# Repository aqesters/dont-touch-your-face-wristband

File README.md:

# dont-touch-your-face-wristband
A wristband that vibrates when the wearer tries to touch their face

## System overview
First of all, the device must be worn on the inside of the wrist, facing towards the body when one's arm is by their side. 

The wristband functions by using two sensors: an accelerometer to measure arm position, and an IR optical sensor to measure proximity. The workflow is described below.
- The microcontroller remains in Sleep mode to conserve power until the arm is raised.
- Once the arm is raised - which is determined by an accelerometer threshold - the accelerometer wakes the microcontroller (MCU) via pin interrupt.
- The MCU remains in Active mode while the arm is raised. In Active mode, the MCU continuously polls the proximity sensor.
- If the proximity reading surpasses a certain threshold, the MCU triggers the vibration motor to alert the wearer.

Note that an alert will not be sent to the wearer unless both the arm is raised (accelerometer threshold) and the hand is close to the face (proximity threshold). This increases the likelihood that the wearer receives a vibration alert only if their hand is near their neck face.

## Cover glass for proximity sensor
In the assembly, the proximity sensor is purposely placed near the edge of the board. At this position, the sensor can detect proximity both above and beside the PCB. If using a cover glass, the following conditions must be met for best performance:
1. The cover glass must be made of IR-transparent material
2. The proximity sensor threshold may need to be increased, as cover glass will reflect some IR back to the sensor 
3. The cover glass should be curved such that the proximity sensor is sensitive to detection both above and near the edge of the PCB (see example)

Note that this implementation for proximity sensing is **PATENT PENDING**.

## Enclosure
The enclosure has been designed to be 3D-printable using PLA and a 0.2 mm nozzle. The design is compatible with off-the-shelf 18 mm wrist straps (see link).

[Amazon link to wrist straps](https://www.amazon.com/dp/B0C1RQ1HML)

The enclosure consists of a "bottom" (which the PCB sits in) and a "lid" (which is glued to the "bottom" to cover the PCB). The enclosure was designed using Onshape. The STEP files are included in `enclosure/`, and the Onshape design file can be accessed at the link below.

[Link to Onshape CAD file](https://cad.onshape.com/documents/f453aeea43687b5a9c082ca3/w/8d4d5c0042ac79ddd7b31543/e/8a52f216663301647b5c429d?renderMode=0&uiState=697bc61246433338537cc1be)

## Electronics
The Kicad design files, Gerber files, component datasheets, and bill of materials (BOM) are included in `electronics/`. The BOM includes components that can be assembled onto the board by PCB manufacturers. Not included in the BOM are the lithium polymer battery and the vibration motor. Links for those are provided below.

### Battery
The battery used in the initial version is a lithium polymer battery with a capacity of 110 mAh and dimensions of 28mm x 12mm x 4mm. The battery leads must be soldered to pads on the PCB.

The link points to a battery from LiPol battery, product number LP401228. Note that this is a foreign provider, and foreign shipping can be expensive. *It might be possible to find a **more convenient** LiPo battery vendor that can provide batteries with similar dimensions.*

[LiPo battery link](https://www.lithium-polymer-battery.net/8mah-200mah-3-7v-lithium-polymer-battery/?_gl=1*131f0fd*_up*MQ..*_gs*MQ..&gclid=Cj0KCQiAp-zLBhDkARIsABcYc6uI_U1x1whldtsxuwOGvXzmkzbKdzTadPaN4wI3JUhvP9JeFW5L0iYaApc_EALw_wcB&gbraid=0AAAAApXvFRnggWyuhWJ-bcXAyFbujbzTa)

### Vibration motor
The motor used in the initial version is a brushed DC haptic motor from Vybronics. These can be purchased from Digikey. The motor leads must be soldered to pads on the PCB.

[Vibration motor link](https://www.digikey.com/en/products/detail/vybronics-inc/VCLP0820B004L/10285889)

## Firmware
The initial version uses an ATtiny85 microcontroller, and the firmware is written and compiled using the Arduino IDE with AtTinyCore board configuration. The Arduino file can be found in `firmware/`.

There are custom drivers for the IR proximity sensor and the battery gauge (present on board, but not yet used by firmware). These drivers are required by the MCU firmware to communicate with these components. These can be found in `firmware/libraries/` and must be included in the Arduino libraries path on the machine compiling the firmware (typical path is `~/Arduino/libraries`).

## Known issues
### No easy way to upload firmware
In-system programming (ISP) is not trivial for the ATtiny85 MCU due to the limited number of pins. The pins used for ISP are also used for I2C communication by the MCU. This is a limitation of the MCU itself, which is limited in its number of pins and features.

----- Potential solution -----

Implement BOTH of the following:
- Add series resistors (470 Ohms) on the PB0 and PB2 pins of the MCU.
- Add pads shorted to MCU Pins *VCC*, *GND*, *PB0*, *PB1*, *PB2*, and *PB5* to the board layout. These pads can be used in an ISP layout to re-program the MCU in place.

### IR proximity sensor VCNL4020 is at End-Of-Life
Vishay Semiconductor no longer sells the VCNL4020 sensor included in this design. However, the VCNL4030X1 is supported and is very similar, though it uses a different footprint.

----- Potential solution -----

Replace VCNL4020 sensor with VCNL4030X1 sensor. Replace the VCNL4020 part with the VCNL4030X1 part in the Kicad schematic and layout (symbol and footprint files already included). Create a driver for VCNL4030X1 using the VCNL4020 driver (in `firmware/libraries/`) as a starting point. 

### Unclear assembly directions for entire part 
The assembly instructions could be clearer, including the best order of operations (e.g., first cut wires to this length for battery and motor, then solder motor, then solder battery, etc...). I will try to expand on assembly instructions in the future. In the meantime, feel free to reach out to me with any questions.

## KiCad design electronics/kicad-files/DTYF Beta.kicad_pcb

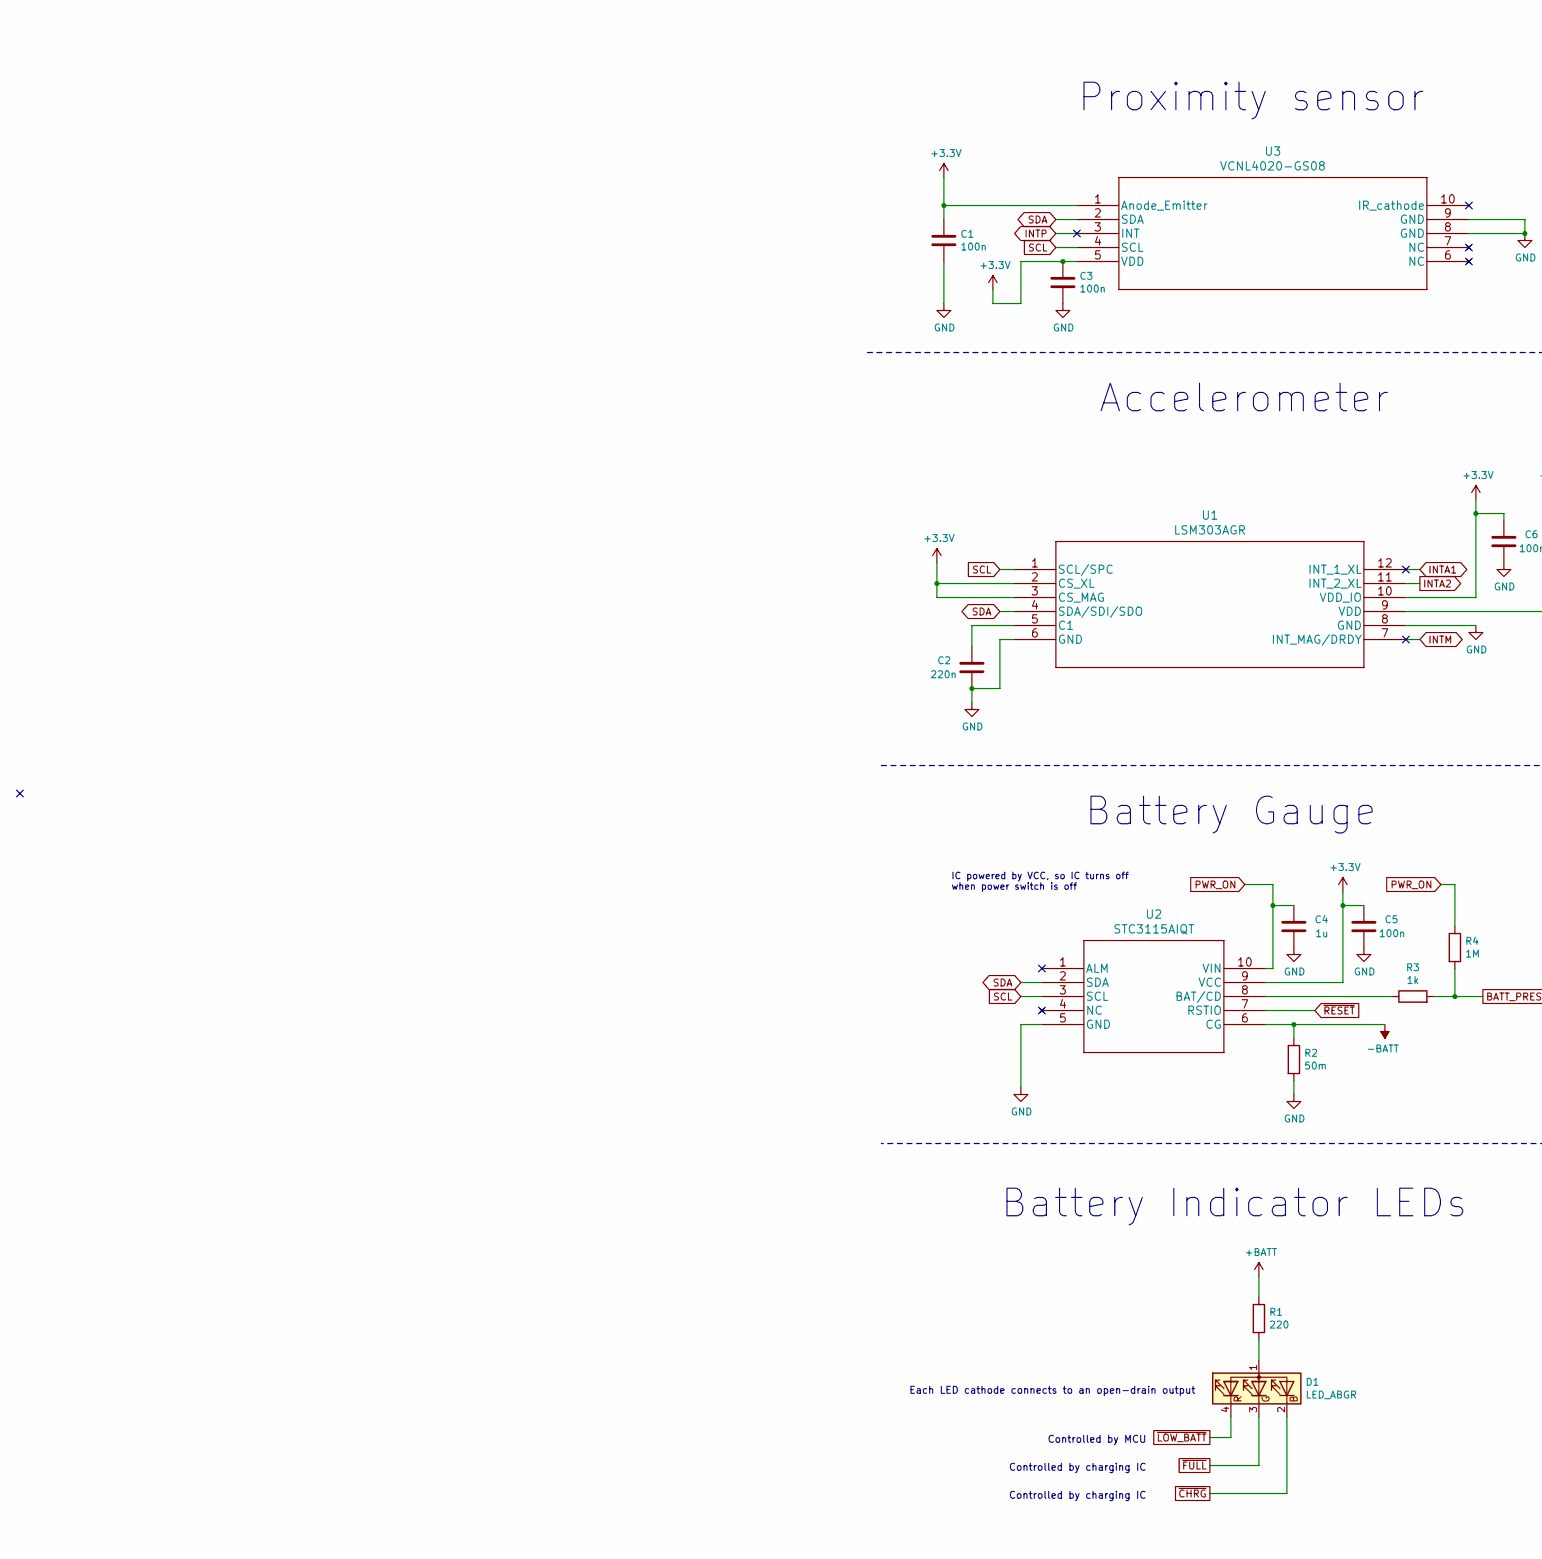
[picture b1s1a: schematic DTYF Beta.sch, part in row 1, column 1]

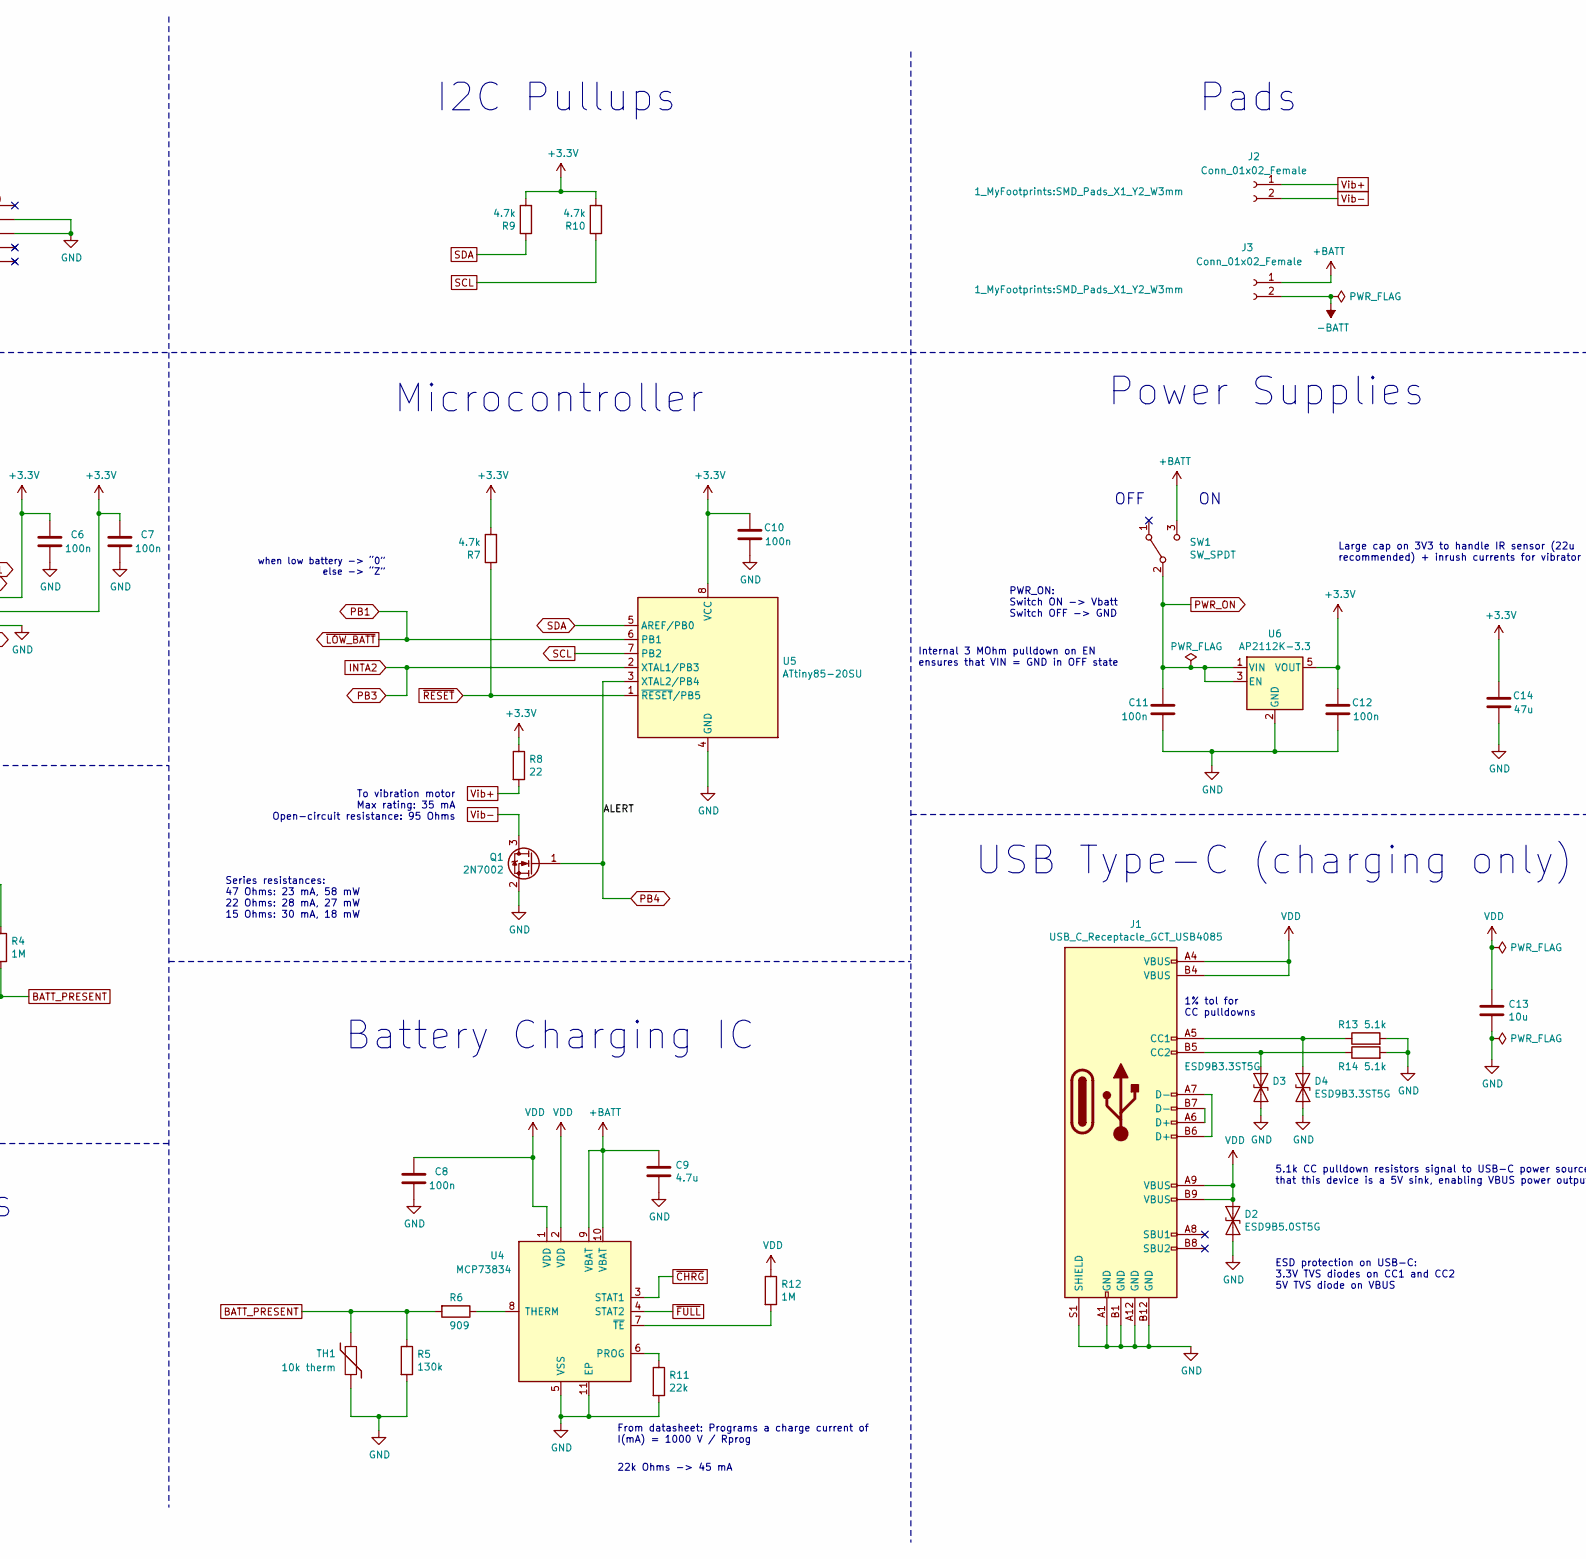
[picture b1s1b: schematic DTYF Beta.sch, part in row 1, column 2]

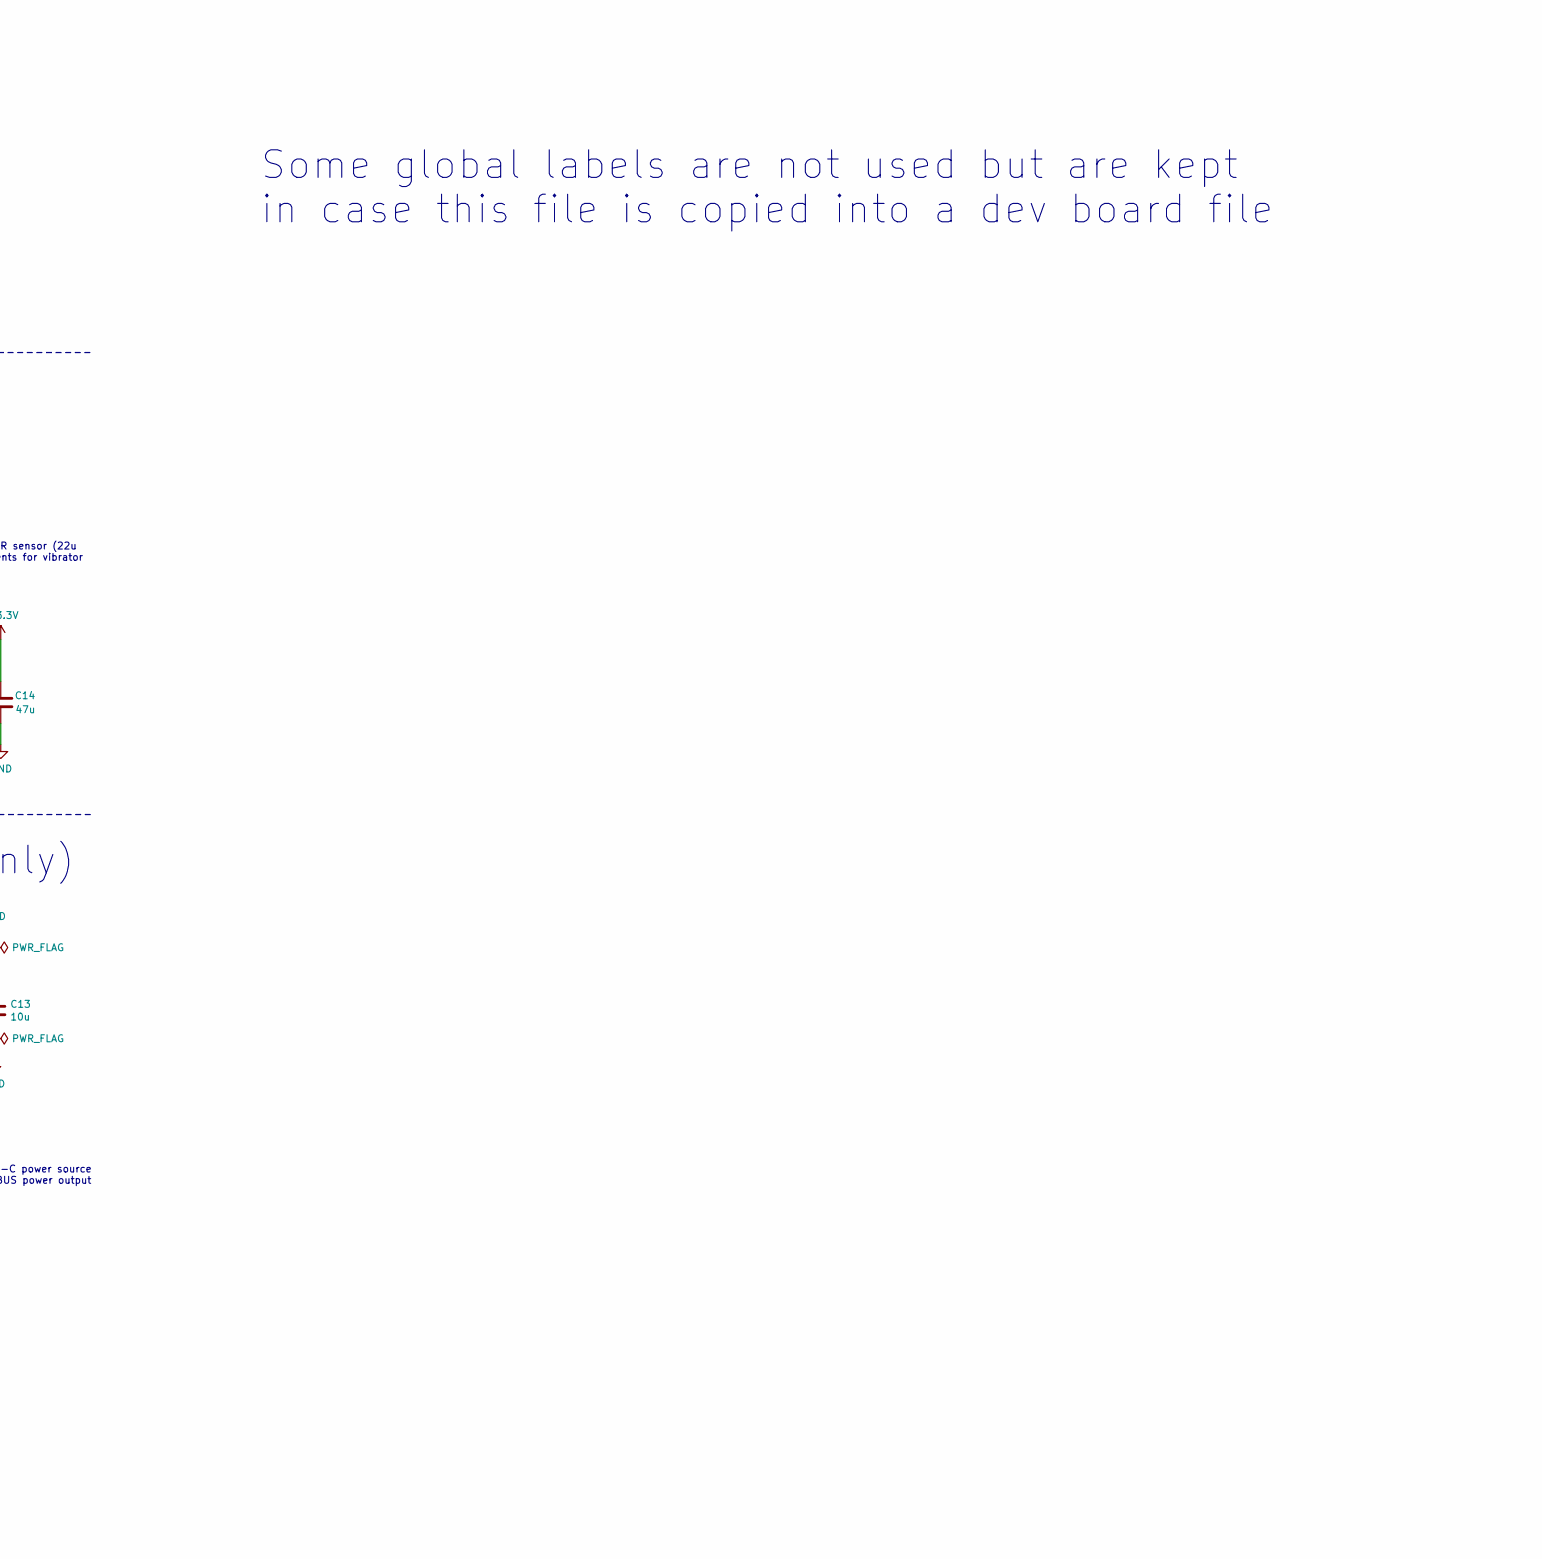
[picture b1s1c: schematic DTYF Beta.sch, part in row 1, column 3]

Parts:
C1, C3, C5, C6, C7, C8, C10, C11, C12: 100n; C_0402_1005Metric
C2: 220n; C_0402_1005Metric
C4: 1u; C_0402_1005Metric
C9: 4.7u; C_0402_1005Metric
C13: 10u; C_0402_1005Metric
C14: 47u; C_0805_2012Metric
D1: LED_ABGR; LED_Cree-PLCC4_2x2mm_CW
D2: ESD9B5.0ST5G; D_SOD-923
D3, D4: ESD9B3.3ST5G; D_SOD-923
J1: USB_C_Receptacle_GCT_USB4085
J2, J3: Conn_01x02_Female; SMD_Pads_X1_Y2_W3mm
Q1: 2N7002; SOT-23
R1: 220; R_0603_1608Metric
R2: 50m; R_0402_1005Metric
R3: 1k; R_0402_1005Metric
R4, R12: 1M; R_0402_1005Metric
R5: 130k; R_0402_1005Metric
R6: 909; R_0402_1005Metric
R7, R9, R10: 4.7k; R_0402_1005Metric
R8: 22; R_0603_1608Metric
R11: 22k; R_0402_1005Metric
R13, R14: 5.1k; R_0402_1005Metric
SW1: SW_SPDT; SW_SPDT_CK-JS102011JAQN
TH1: 10k therm; R_0402_1005Metric
U1: LSM303AGR
U2: STC3115AIQT
U3: VCNL4020-GS08
U4: MCP73834; MCP73834-CNI&slash_MF
U5: ATtiny85-20SU; SOIC-8_5.275x5.275mm_P1.27mm
U6: AP2112K-3.3; SOT-23-5

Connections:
+3V3: C1.1, C3.1, C5.1, C6.1, C7.1, C10.1, C12.1, C14.1, R7.2, R8.1, R9.2, R10.2, U1.2 (CS_XL), U1.3 (CS_MAG), U1.9 (VDD), U1.10 (VDD_IO), U2.9 (VCC), U3.1 (Anode_Emitter), U3.5 (VDD), U5.8 (VCC), U6.5 (VOUT)
+BATT: C9.1, J3.1, R1.1, SW1.3 (C), U4.9 (VBAT), U4.10 (VBAT)
-BATT: J3.2, R2.1, U2.6 (CG)
BATT_PRESENT: R3.2, R4.2, R5.1, R6.2, TH1.1
GND: C1.2, C2.2, C3.2, C4.2, C5.2, C6.2, C7.2, C8.2, C9.2, C10.2, C11.2, C12.2, C13.2, C14.2, D2.2 (A2), D3.2 (A2), D4.2 (A2), J1.A1 (GND), J1.A12 (GND), J1.B1 (GND), J1.B12 (GND), J1.S1 (SHIELD), Q1.2 (S), R2.2, R5.2, R11.2, R13.2, R14.2, TH1.2, U1.6 (GND), U1.8 (GND), U2.5 (GND), U3.8 (GND), U3.9 (GND), U4.5 (VSS), U4.11 (EP), U5.4 (GND), U6.2 (GND)
INTA1: U1.12 (INT_1_XL)
INTA2: U1.11 (INT_2_XL), U5.2 (XTAL1/PB3)
INTM: U1.7 (INT_MAG/DRDY)
INTP: U3.3 (INT)
unnamed: C2.1, U1.5 (C1)
unnamed: D1.1 (A), R1.2
unnamed: D3.1 (A1), J1.B5 (CC2), R14.1
unnamed: D4.1 (A1), J1.A5 (CC1), R13.1
unnamed: J1.A6 (D+), J1.B7 (D-)
unnamed: J1.A7 (D-), J1.B6 (D+)
unnamed: R3.1, U2.8 (BAT/CD)
unnamed: R6.1, U4.8 (THERM)
unnamed: R11.1, U4.6 (PROG)
unnamed: R12.2, U4.7 (~TE)
PB1: D1.4 (RK), U5.6 (PB1)
PB4: Q1.1 (G), U5.3 (XTAL2/PB4)
PWR_ON: C4.1, C11.1, R4.1, SW1.2 (B), U2.10 (VIN), U6.1 (VIN), U6.3 (EN)
SCL: R10.1, U1.1 (SCL/SPC), U2.3 (SCL), U3.4 (SCL), U5.7 (PB2)
SDA: R9.1, U1.4 (SDA/SDI/SDO), U2.2 (SDA), U3.2 (SDA), U5.5 (AREF/PB0)
VDD: C8.1, C13.1, D2.1 (A1), J1.A4 (VBUS), J1.A9 (VBUS), J1.B4 (VBUS), J1.B9 (VBUS), R12.1, U4.1 (VDD), U4.2 (VDD)
Vib+: J2.1, R8.2
Vib-: J2.2, Q1.3 (D)
~CHRG: D1.2 (BK), U4.3 (STAT1)
~FULL: D1.3 (GK), U4.4 (STAT2)
~RESET: R7.1, U2.7 (RSTIO), U5.1 (~RESET~/PB5)

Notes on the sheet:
Microcontroller
Series resistances: 47 Ohms: 23 mA, 58 mW 22 Ohms: 28 mA, 27 mW 15 Ohms: 30 mA, 18 mW
Accelerometer
Pads
Battery Indicator LEDs
Power Supplies
Battery Charging IC
Battery Gauge
I2C Pullups
From datasheet: Programs a charge current of I(mA) = 1000 V / Rprog
To vibration motor Max rating: 35 mA Open-circuit resistance: 95 Ohms
USB Type-C (charging only)
22k Ohms -> 45 mA
when low battery -> “0” else -> “Z”
Each LED cathode connects to an open-drain output
1% tol for CC pulldowns
5.1k CC pulldown resistors signal to USB-C power source that this device is a 5V sink, enabling VBUS power output
Controlled by MCU
IC powered by VCC, so IC turns off when power switch is off
Proximity sensor
OFF
PWR_ON: Switch ON -> Vbatt Switch OFF -> GND
Some global labels are not used but are kept in case this file is copied into a dev board file
Controlled by charging IC
Internal 3 MOhm pulldown on EN ensures that VIN = GND in OFF state
Large cap on 3V3 to handle IR sensor (22u recommended) + inrush currents for vibrator
ESD protection on USB-C: 3.3V TVS diodes on CC1 and CC2 5V TVS diode on VBUS

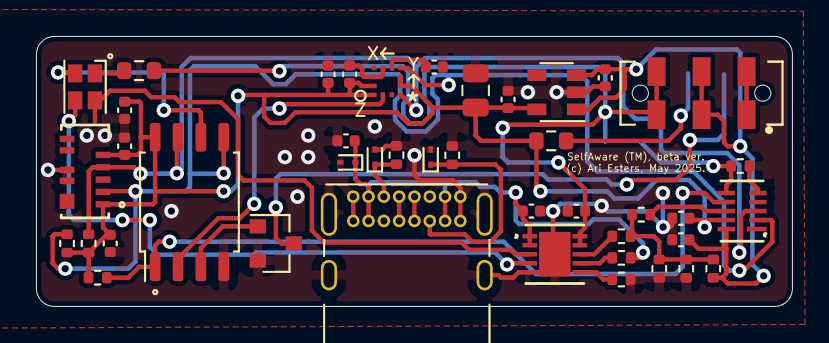
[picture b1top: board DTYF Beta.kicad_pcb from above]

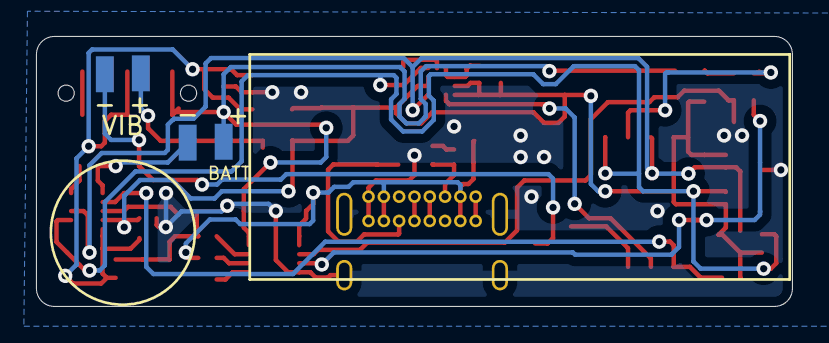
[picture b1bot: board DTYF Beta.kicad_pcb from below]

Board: 2 copper layers, 42.0 x 15.0 mm, 44 parts (2 on the bottom side), 27 nets.

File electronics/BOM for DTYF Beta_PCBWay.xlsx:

|  |  | Bill of Materials for DTYF Beta
Item # | *Designator | *Qty | Manufacturer | *Mfg Part # | Description / Value | *Package/Footprint | Type | Your Instructions / Notes
1.0 | C1, C3, C5, C6, C7, C8, C10, C11, C12 | 9.0 | Samsung Electro-Mechanics | CL05B104KP5NNNC | Unpolarized capacitor 100nF | 0402 | SMD
2.0 | C2, | 1.0 | Samsung Electro-Mechanics | CL05B224KO5NNNC | Unpolarized capacitor 220nF | 0402 | SMD
3.0 | C4, | 1.0 | Samsung Electro-Mechanics | CL05A105KO5NNNC | Unpolarized capacitor 1uF | 0402 | SMD
4.0 | C9, | 1.0 | Samsung Electro-Mechanics | CL05A475KQ5NRNC | Unpolarized capacitor 4.7 uF | 0402 | SMD
5.0 | C13, | 1.0 | Samsung Electro-Mechanics | CL05A106MQ5NUNC | Unpolarized capacitor 10uF | 0402 | SMD
6.0 | C14, | 1.0 | Samsung Electro-Mechanics | CL21A476MQYNNNE | Unpolarized capacitor 47 uF | 0805 | SMD
7.0 | D1, | 1.0 | Cree LED | CLMVC-FKA-CL1D1L71BB7C3C3 | RGB LED, anode/blue/green/red | PLCC4_2X2mm_CW | SMD | Pad 1 marked on PCB layout
8.0 | D2, | 1.0 | onsemi | ESD9B5.0ST5G | ESD protection diode, 5.0Vrwm | SOD-923 | SMD
9.0 | D3, D4, | 2.0 | onsemi | ESD9B3.3ST5G | ESD protection diode, 3.3Vrwm | SOD-923 | SMD
10.0 | J1, | 1.0 | GCT | USB4085-GF-A | USB-C receptacle connector USB4085 | GCT-USB4085 | Thru-hole
11.0 | J2, J3, | 2.0 | - | - | Custom SMD pads for customer use | - | DNI | DNI - No parts specified
12.0 | Q1, | 1.0 | onsemi | 2N7002 | 0.115A Id, 60V Vds, N-Channel MOSFET | SOT-23 | SMD
13.0 | R1, | 1.0 | YAGEO | RC0603FR-07220RL | Resistor 220 Ohms | 0603 | SMD
14.0 | R2, | 1.0 | Panasonic Electronic Components | ERJ-2BWFR050X | Current sense resistor 50 mOhms, 1% tolerance | 0402 | SMD | If replaced, tolerance must be 1% max
15.0 | R3, | 1.0 | Panasonic Electronic Components | ERJ-2RKF1001X | Resistor 1k | 0402 | SMD
16.0 | R4, R12, | 2.0 | Panasonic Electronic Components | ERJ-2RKF1004X | Resistor 1M | 0402 | SMD
17.0 | R5, | 1.0 | Panasonic Electronic Components | ERJ-2RKF1303X | Resistor 130k | 0402 | SMD
18.0 | R6, | 1.0 | Panasonic Electronic Components | ERA-2AEB9090X | Resistor 909 | 0402 | SMD
19.0 | R7, R9, R10, | 3.0 | Panasonic Electronic Components | ERJ-2GEJ472X | Resistor 4.7k | 0402 | SMD
20.0 | R8, | 1.0 | Panasonic Electronic Components | ERJ-3EKF22R0V | Resistor 22 | 0603 | SMD
21.0 | R11, | 1.0 | Panasonic Electronic Components | ERJ-2GEJ223X | Resistor 22k | 0402 | SMD
22.0 | R13, R14, | 2.0 | Panasonic Electronic Components | ERJ-2GEJ512X | Resistor 5.1k | 0402 | SMD
23.0 | SW1, | 1.0 | C&K | JS102011JAQN | Switch, single pole double throw (SPDT) | SW_SPDT_CK-JS102011JAQN | SMD | Pad 1 marked on PCB layout
24.0 | TH1, | 1.0 | Murata Electronics | NCU15XH103F6SRC | NTC 10k, temperature-dependent resistor | 0402 | SMD
25.0 | U1, | 1.0 | STMicroelectronics | LSM303AGRTR | IMU, accelerometer + magnetometer | LGA-12 | SMD | Pad 1 marked on PCB layout
26.0 | U2, | 1.0 | STMicroelectronics | STC3115AIQT | IC battery monitor | DFN-10 | SMD | Pad 1 marked on PCB layout
27.0 | U3, | 1.0 | Vishay Semiconductor | VCNL4020-GS08 | Optical sensor, IR and ambient | VDFN-10 | SMD | Pad 1 marked on PCB layout
28.0 | U4, | 1.0 | Microchip Technology | MCP73834-CNI/MF | IC single-cell battery control | DFN-10 | SMD | Pad 1 marked on PCB layout
29.0 | U5, | 1.0 | Microchip Technology | ATTINY85-20SU | AtTiny85 MCU, 8kB Flash, 512B SRAM, 512B EEPROM | SOIC-8 | DNI | DNI - I will program and install
30.0 | U6, | 1.0 | Diodes Incorporated | AP2112K-3.3TRG1 | 3.3V / 600mA LDO regulator with enable pin | SOT-25 | SMD | Pad 1 marked on PCB layout
 |  | 44
Need a quick and accurante quote? Need an efficient production? Please read SMT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
Click for Instructions on How to Create a BOM

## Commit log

2026-01-29 Adding project details to README
    Including system overview and notes on enclosure design, electronics specifications, firmware information, and known issues.
2026-01-29 Change image formats to JPG
2026-01-29 Fixed image and URL links
    Fixed image and URL links
2026-01-29 Lowered image res

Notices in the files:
parts and their libraries:
Copyright 2016 Accelerated Designs. All rights reserved.
